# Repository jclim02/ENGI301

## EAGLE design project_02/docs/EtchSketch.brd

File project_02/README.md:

# Etch-a-Sketch
 
Create a PCB for an etch-a-sketch.

## /docs
Includes: BOM (.csv), schematics PDF, CAM-generated files, pictures of top and bottom layout (.pdf), initial mechanical block diagram

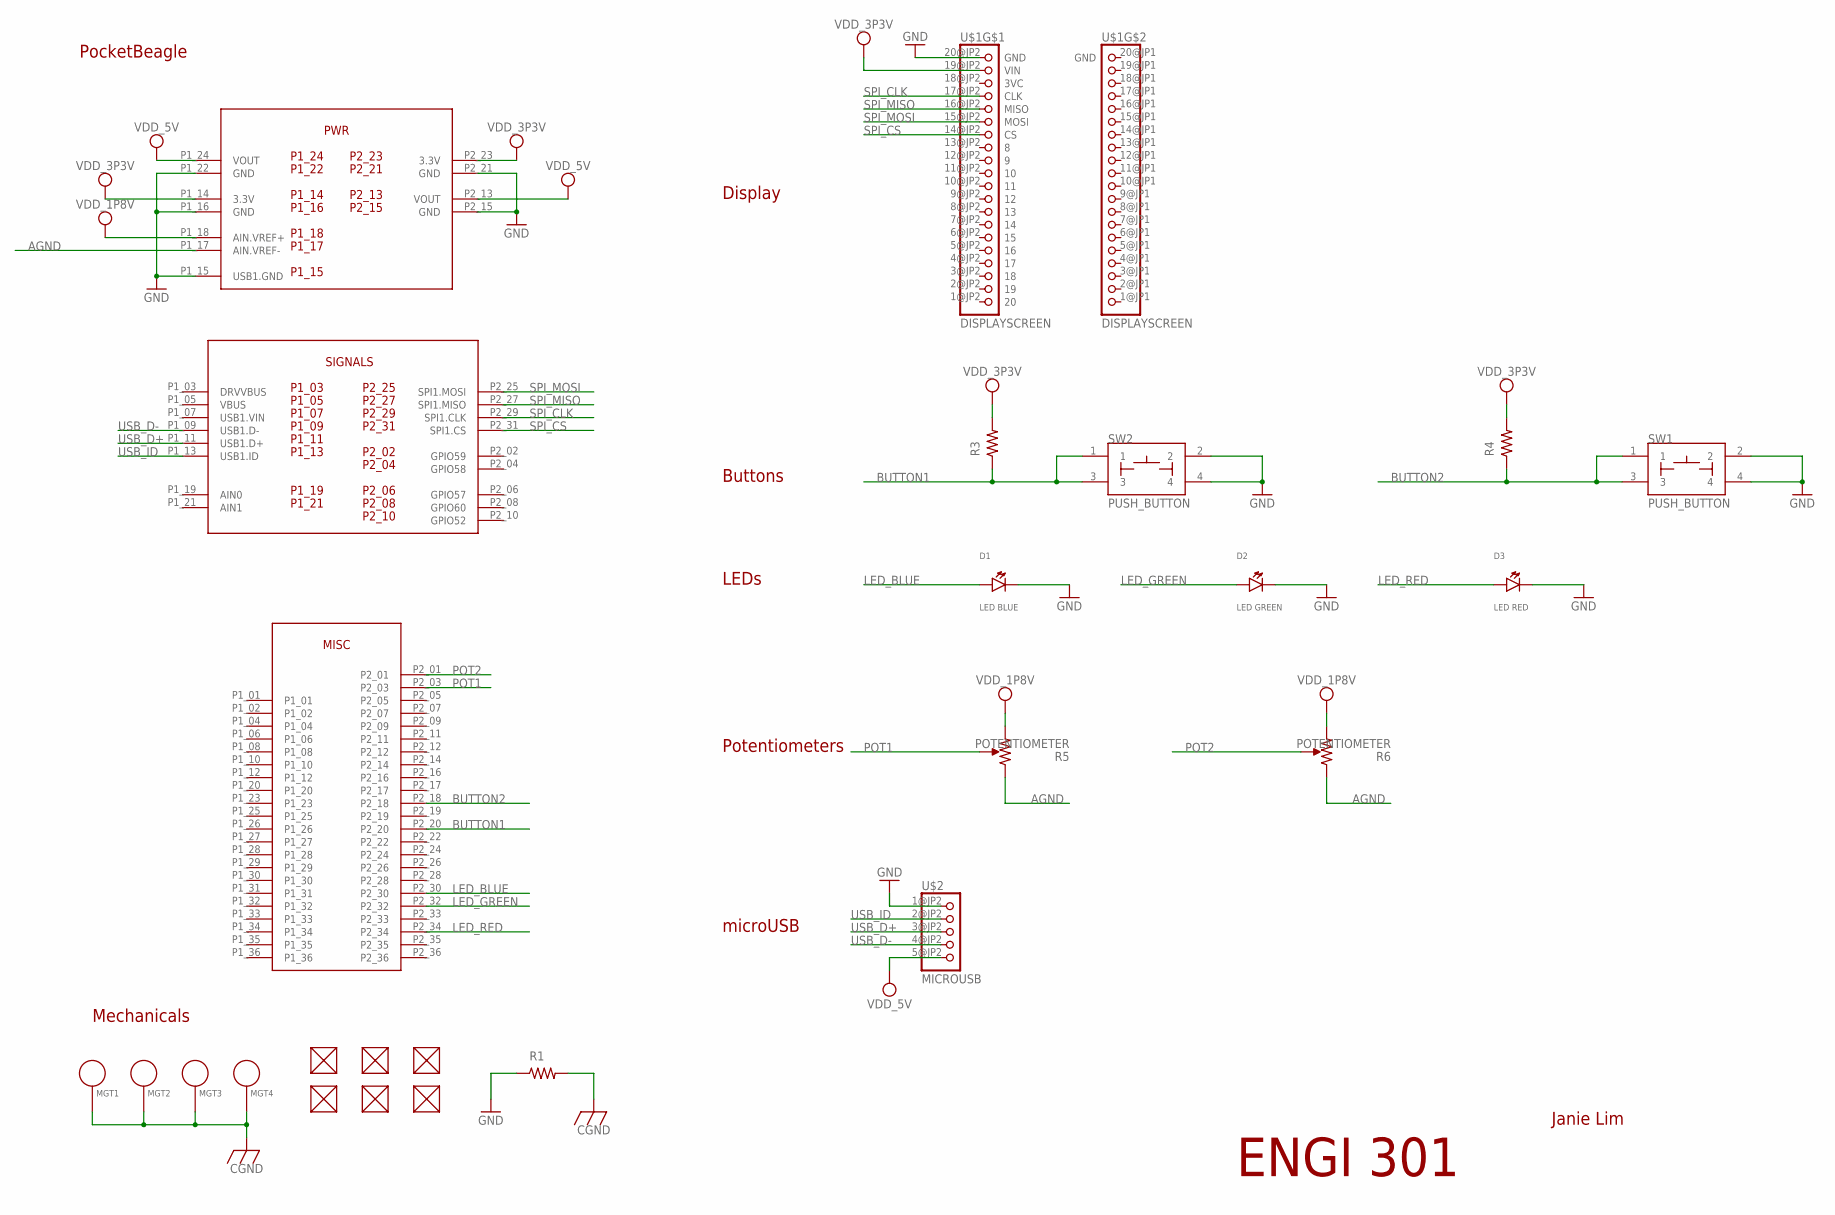
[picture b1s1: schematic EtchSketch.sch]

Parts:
D1: LED BLUE; EIA-STD
D2: LED GREEN; EIA-STD
D3: LED RED; EIA-STD
FUD1, FUD2, FUD3, FUD4, FUD5, FUD6: FIDUCIAL; FIDUCIAL_40MIL
MGT1, MGT2, MGT3, MGT4: MOUNTING_HOLE
R1, R3, R4: R_R0603; R0603
R5, R6: POTENTIOMETER; POT-PO90S
SW1, SW2: PUSH_BUTTON; BUTTON_12.5MM
U1: POCKETBEAGLE_NEW; POCKETBEAGLE
U$1: DISPLAYSCREEN
U$2: MICROUSB

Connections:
AGND: R5.CCW, R6.CCW, U1.P1_17 (AIN.VREF-)
BUTTON1: R3.1, SW2.1, SW2.3, U1.P2_20
BUTTON2: R4.1, SW1.1, SW1.3, U1.P2_18
CGND: MGT1.P$1, MGT2.P$1, MGT3.P$1, MGT4.P$1, R1.2
GND: D1.CATHODE, D2.CATHODE, D3.CATHODE, R1.1, SW1.2, SW1.4, SW2.2, SW2.4, U1.P1_15 (USB1.GND), U1.P1_16 (GND), U1.P1_22 (GND), U1.P2_15 (GND), U1.P2_21 (GND), U$1.20@JP2 (GND), U$2.1@JP2 (GND)
LED_BLUE: D1.ANODE, U1.P2_30
LED_GREEN: D2.ANODE, U1.P2_32
LED_RED: D3.ANODE, U1.P2_34
POT1: R5.S, U1.P2_03
POT2: R6.S, U1.P2_01
SPI_CLK: U1.P2_29 (SPI1.CLK), U$1.17@JP2 (CLK)
SPI_CS: U1.P2_31 (SPI1.CS), U$1.14@JP2 (CS)
SPI_MISO: U1.P2_27 (SPI1.MISO), U$1.16@JP2 (MISO)
SPI_MOSI: U1.P2_25 (SPI1.MOSI), U$1.15@JP2 (MOSI)
USB_D+: U1.P1_11 (USB1.D+), U$2.3@JP2 (D+)
USB_D-: U1.P1_09 (USB1.D-), U$2.4@JP2 (D-)
USB_ID: U1.P1_13 (USB1.ID), U$2.2@JP2 (ID)
VDD_1P8V: R5.CW, R6.CW, U1.P1_18 (AIN.VREF+)
VDD_3P3V: R3.2, R4.2, U1.P1_14 (3.3V), U1.P2_23 (3.3V), U$1.19@JP2 (VIN)
VDD_5V: U1.P1_24 (VOUT), U1.P2_13 (VOUT), U$2.5@JP2 (5V)

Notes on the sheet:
ENGI 301
Janie Lim
microUSB
Potentiometers
LEDs
Buttons
Display
PocketBeagle
Mechanicals

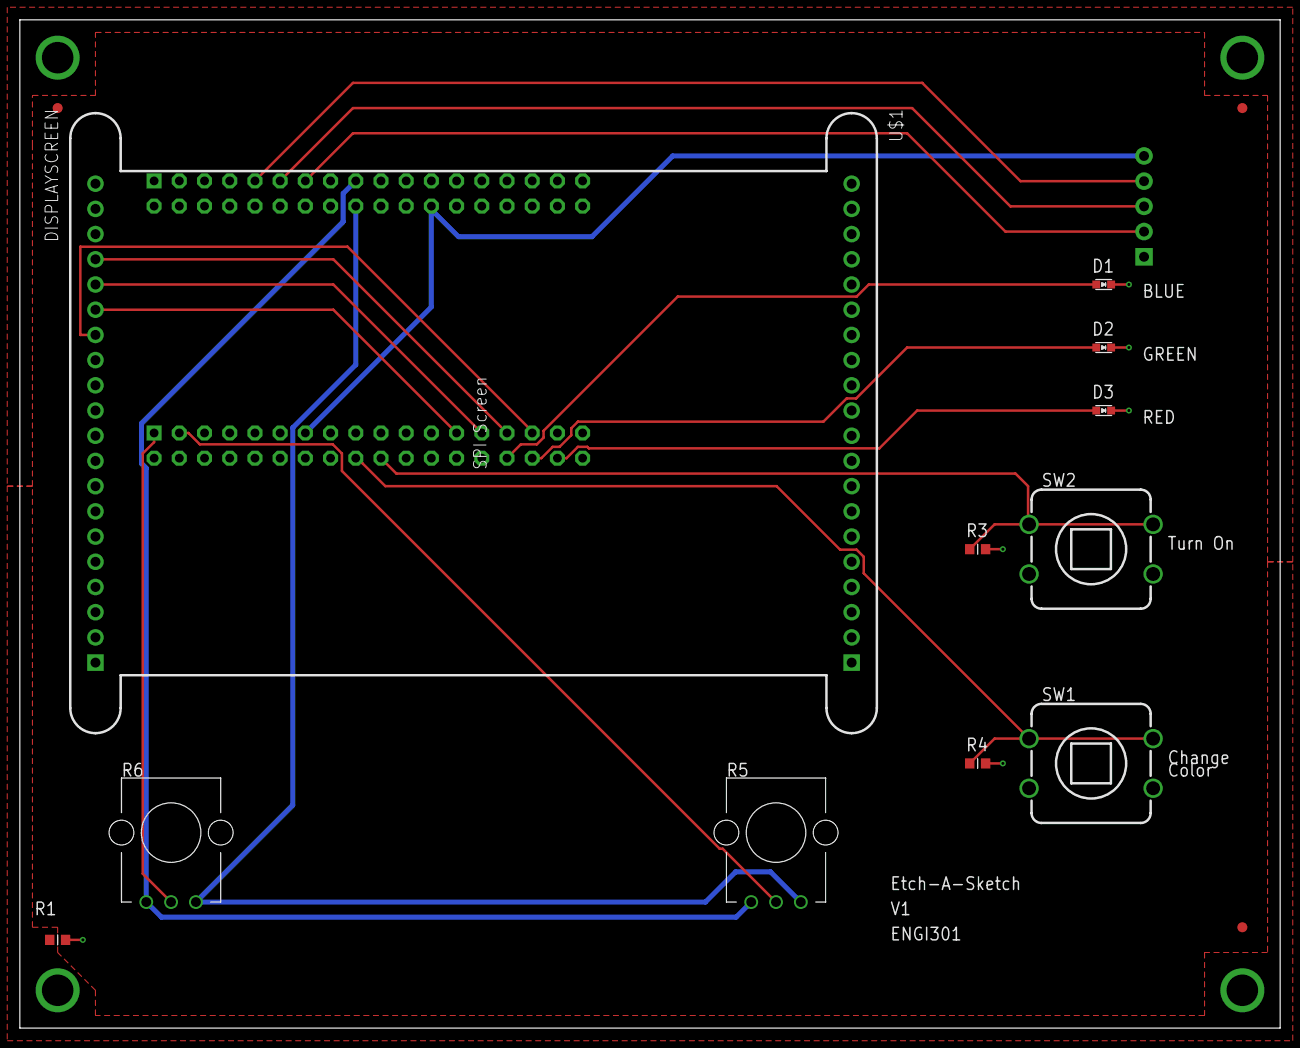
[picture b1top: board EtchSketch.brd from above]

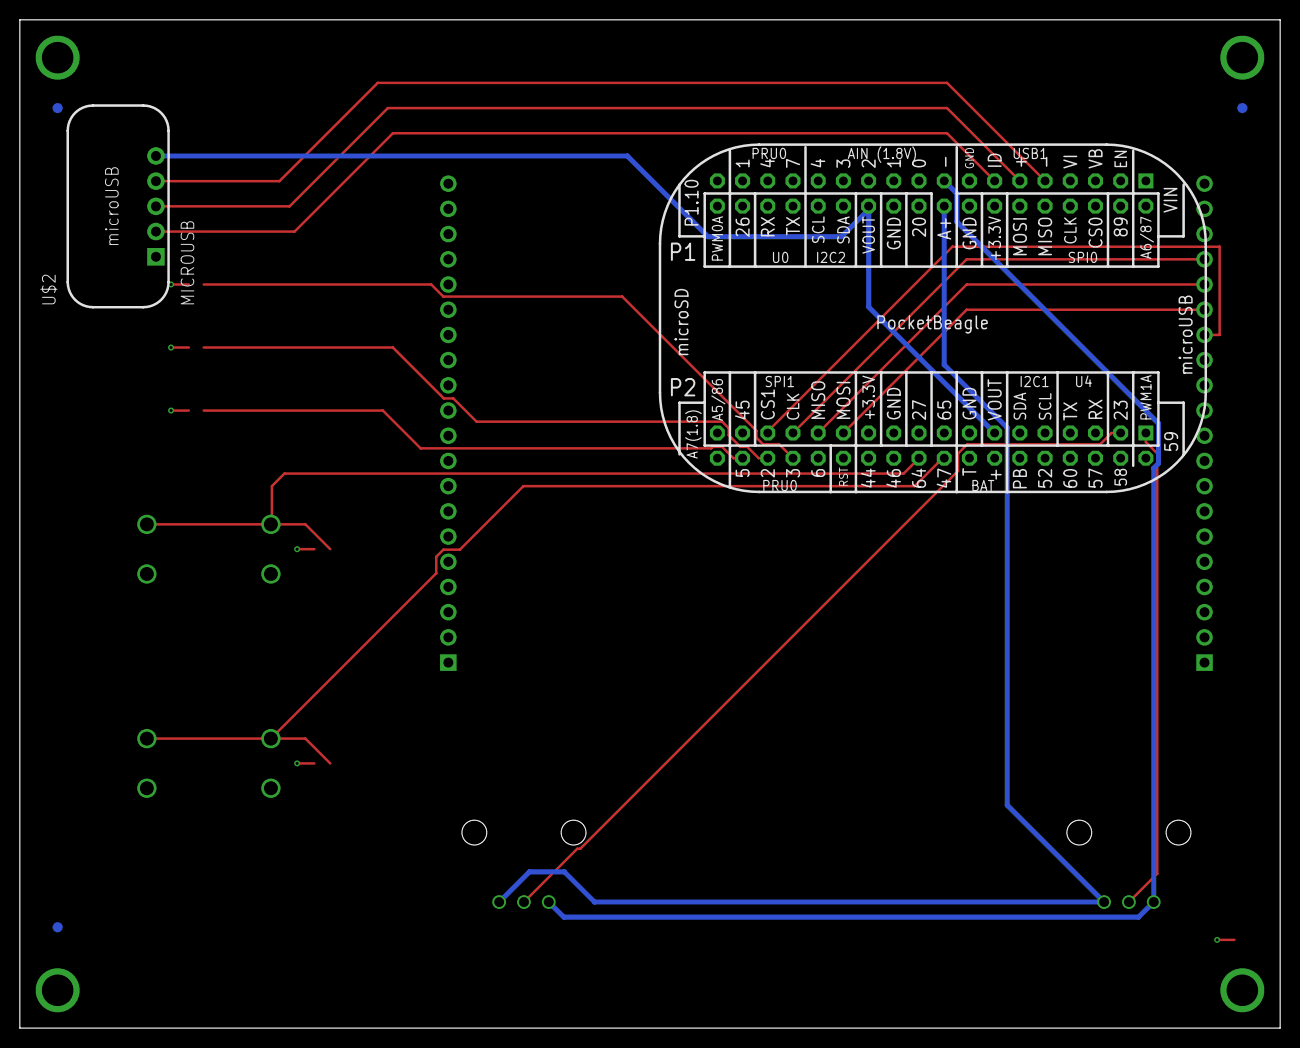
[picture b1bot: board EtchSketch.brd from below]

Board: 4 copper layers, 127.0 x 101.6 mm, 23 parts (5 on the bottom side), 20 nets.

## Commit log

2023-02-14 Create del
2023-02-14 add simple_calc
2023-02-14 blink_USR3
2023-02-14 led blink update
2023-02-14 Update blinking Hz
2023-02-14 modified button
2023-02-14 additional button work
2023-02-14 modified button code
2023-02-14 still not working
2023-02-15 fixed first two parts
2023-02-15 fixed timing issue
2023-02-17 with updated parts list
2023-03-07 added software framework
2023-03-31 ENGI301
2023-04-03 Revised Software Framework
2023-04-03 Final Draft 1
2023-04-03 new folder
2023-04-03 older version of software framework
2023-04-25 updated system block diagram
2023-05-02 Create delete
2023-05-02 schematics
2023-05-02 .sch
2023-05-02 .brd
2023-05-02 bottom layout
2023-05-02 top layout
2023-05-02 assembly files
2023-05-02 drill file
2023-05-02 gerber files
2023-05-02 library
2023-05-02 manufacturing screenshots
